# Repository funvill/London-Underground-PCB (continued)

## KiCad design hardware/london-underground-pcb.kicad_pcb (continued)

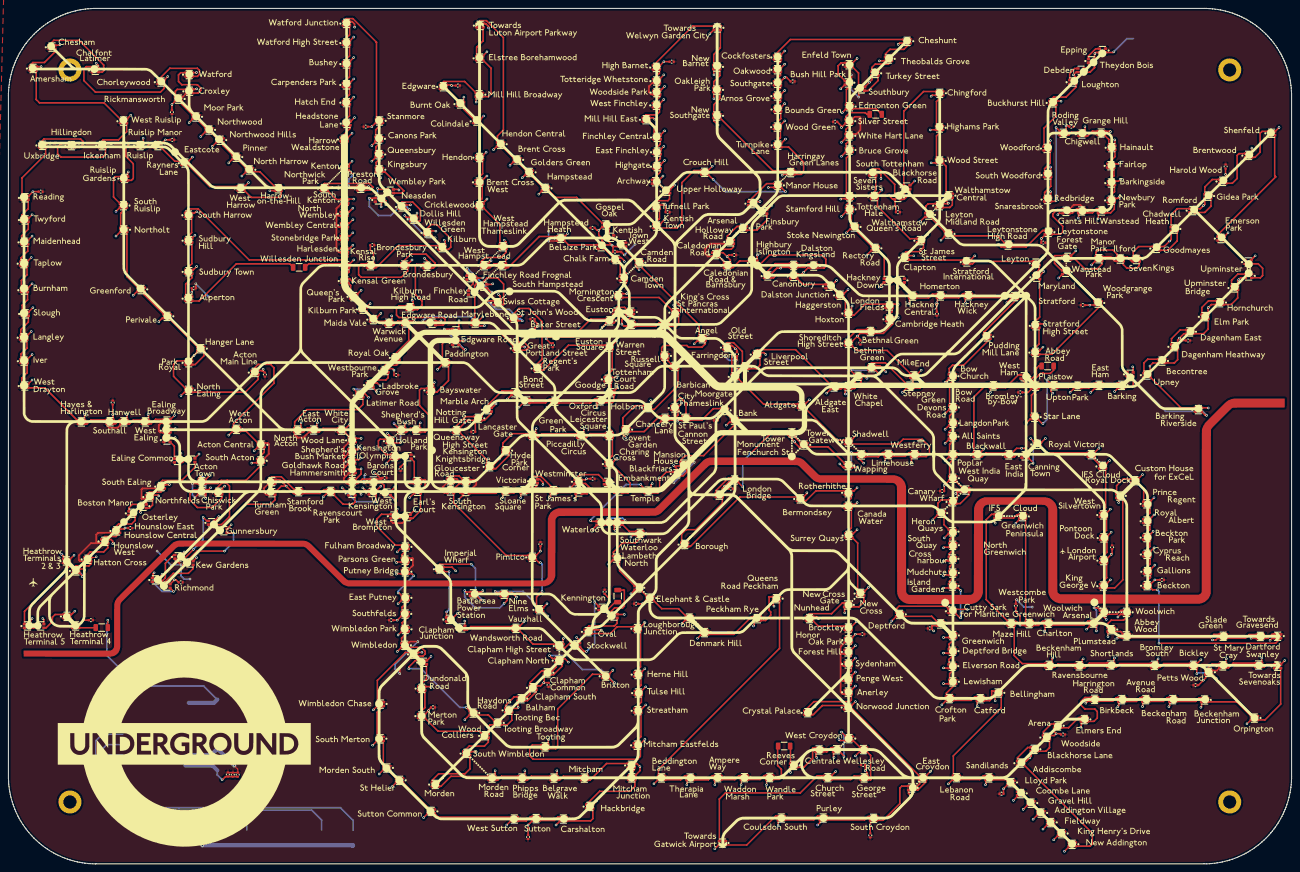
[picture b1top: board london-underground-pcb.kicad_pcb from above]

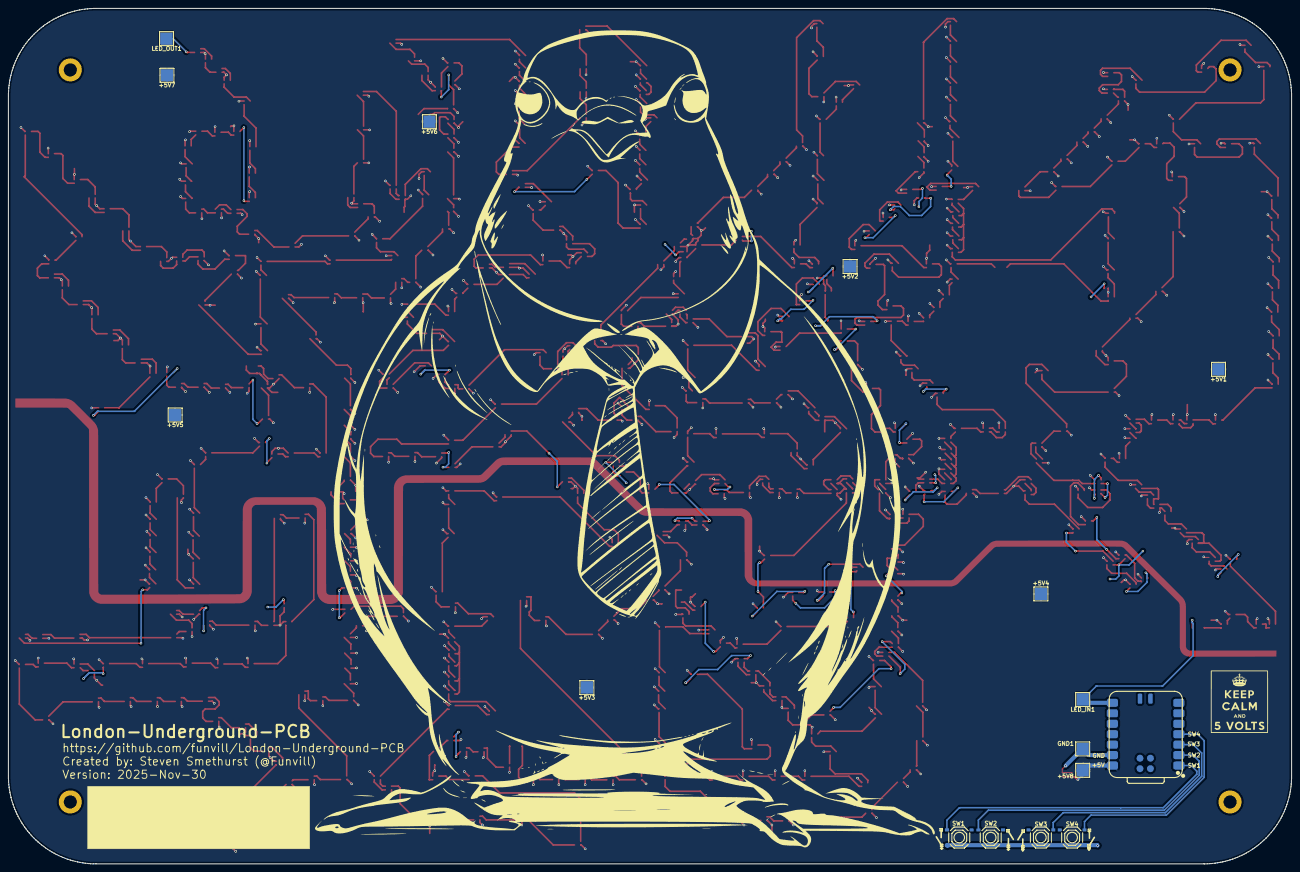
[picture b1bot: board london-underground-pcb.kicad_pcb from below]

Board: 2 copper layers, 312.0 x 208.0 mm, 655 parts (16 on the bottom side), 582 nets.

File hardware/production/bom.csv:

Designator,Footprint,Quantity,Value,LCSC Part #
"+5V1, +5V2, +5V3, +5V4, +5V5, +5V6, +5V7, +5V8, GND1, LED_IN1, LED_OUT1",TestPoint_Pad_3.0x3.0mm,11,TestPoint,
"LED1, LED10, LED100, LED101, LED102, LED103, LED104, LED105, LED106, LED107, LED108, LED109, LED11, LED110, LED111, LED112, LED113, LED114, LED115, LED116, LED117, LED118, LED119, LED12, LED120, LED121, LED122, LED123, LED124, LED125, LED126, LED127, LED128, LED129, LED13, LED130, LED131, LED132, LED133, LED134, LED135, LED136, LED137, LED138, LED139, LED14, LED140, LED141, LED142, LED143, LED144, LED145, LED146, LED147, LED148, LED149, LED15, LED150, LED151, LED152, LED153, LED154, LED155, LED156, LED157, LED158, LED159, LED16, LED160, LED161, LED162, LED163, LED164, LED165, LED166, LED167, LED168, LED169, LED17, LED170, LED171, LED172, LED173, LED174, LED175, LED176, LED177, LED178, LED179, LED18, LED180, LED181, LED182, LED183, LED184, LED185, LED186, LED187, LED188, LED189, LED19, LED190, LED191, LED192, LED193, LED194, LED195, LED196, LED197, LED198, LED199, LED2, LED20, LED200, LED201, LED202, LED203, LED204, LED205, LED206, LED207, LED208, LED209, LED21, LED210, LED211, LED212, LED213, LED214, LED215, LED216, LED217, LED218, LED219, LED22, LED220, LED221, LED222, LED223, LED224, LED225, LED226, LED227, LED228, LED229, LED23, LED230, LED231, LED232, LED233, LED234, LED235, LED236, LED237, LED238, LED239, LED24, LED240, LED241, LED242, LED243, LED244, LED245, LED246, LED247, LED248, LED249, LED25, LED250, LED251, LED252, LED253, LED254, LED255, LED256, LED257, LED258, LED259, LED26, LED260, LED261, LED262, LED263, LED264, LED265, LED266, LED267, LED268, LED269, LED27, LED270, LED271, LED272, LED273, LED274, LED275, LED276, LED277, LED278, LED279",LED-SMD_4P-L1.6-W1.5_XL-1615RGBC-WS2812B-1,200,XL-1615RGBC-WS2812B,C5349954
"LED28, LED280, LED281, LED282, LED283, LED284, LED285, LED286, LED287, LED288, LED289, LED29, LED290, LED291, LED292, LED293, LED294, LED295, LED296, LED297, LED298, LED299, LED3, LED30, LED300, LED301, LED302, LED303, LED304, LED305, LED306, LED307, LED308, LED309, LED31, LED310, LED311, LED312, LED313, LED314, LED315, LED316, LED317, LED318, LED319, LED32, LED320, LED321, LED322, LED323, LED324, LED325, LED326, LED327, LED328, LED329, LED33, LED330, LED331, LED332, LED333, LED334, LED335, LED336, LED337, LED338, LED339, LED34, LED340, LED341, LED342, LED343, LED344, LED345, LED346, LED347, LED348, LED349, LED35, LED350, LED351, LED352, LED353, LED354, LED355, LED356, LED357, LED358, LED359, LED36, LED360, LED361, LED362, LED363, LED364, LED365, LED366, LED367, LED368, LED369, LED37, LED370, LED371, LED372, LED373, LED374, LED375, LED376, LED377, LED378, LED379, LED38, LED380, LED381, LED382, LED383, LED384, LED385, LED386, LED387, LED388, LED389, LED39, LED390, LED391, LED392, LED393, LED394, LED395, LED396, LED397, LED398, LED399, LED4, LED40, LED400, LED401, LED402, LED403, LED404, LED405, LED406, LED407, LED408, LED409, LED41, LED410, LED411, LED412, LED413, LED414, LED415, LED416, LED417, LED418, LED419, LED42, LED420, LED421, LED422, LED423, LED424, LED425, LED426, LED427, LED428, LED429, LED43, LED430, LED431, LED432, LED433, LED434, LED435, LED436, LED437, LED438, LED439, LED44, LED440, LED441, LED442, LED443, LED444, LED445, LED446, LED447, LED448, LED449, LED45, LED450, LED451, LED452, LED453, LED454, LED455, LED456, LED457, LED458, LED459",LED-SMD_4P-L1.6-W1.5_XL-1615RGBC-WS2812B-1,200,XL-1615RGBC-WS2812B,C5349954
"LED46, LED460, LED461, LED462, LED463, LED464, LED465, LED466, LED467, LED468, LED469, LED47, LED470, LED471, LED472, LED473, LED474, LED475, LED476, LED477, LED478, LED479, LED48, LED480, LED481, LED482, LED483, LED484, LED485, LED486, LED487, LED488, LED489, LED49, LED490, LED491, LED492, LED493, LED494, LED495, LED496, LED497, LED498, LED499, LED5, LED50, LED500, LED501, LED502, LED503, LED504, LED505, LED506, LED507, LED508, LED509, LED51, LED510, LED511, LED512, LED513, LED514, LED515, LED516, LED517, LED518, LED519, LED52, LED520, LED521, LED522, LED523, LED524, LED525, LED526, LED527, LED528, LED529, LED53, LED530, LED531, LED532, LED533, LED534, LED535, LED536, LED537, LED538, LED539, LED54, LED540, LED541, LED542, LED543, LED544, LED545, LED546, LED547, LED548, LED549, LED55, LED550, LED551, LED552, LED553, LED554, LED555, LED556, LED557, LED558, LED559, LED56, LED560, LED561, LED562, LED563, LED564, LED565, LED566, LED567, LED568, LED569, LED57, LED58, LED59, LED6, LED60, LED61, LED62, LED63, LED64, LED65, LED66, LED67, LED68, LED69, LED7, LED70, LED71, LED72, LED73, LED74, LED75, LED76, LED77, LED78, LED79, LED8, LED80, LED81, LED82, LED83, LED84, LED85, LED86, LED87, LED88, LED89, LED9, LED90, LED91, LED92, LED93, LED94, LED95, LED96, LED97, LED98, LED99",LED-SMD_4P-L1.6-W1.5_XL-1615RGBC-WS2812B-1,169,XL-1615RGBC-WS2812B,C5349954
"R1, R2, R3, R4, R5, R6",1206,6,1206W4F0000T5E,C17888
"ROW1, ROW10, ROW11, ROW12, ROW13, ROW14, ROW15, ROW16, ROW17, ROW18, ROW19, ROW2, ROW20, ROW21, ROW22, ROW23, ROW24, ROW25, ROW26, ROW27, ROW28, ROW29, ROW3, ROW30, ROW31, ROW32, ROW33, ROW34, ROW35, ROW36, ROW37, ROW38, ROW39, ROW4, ROW40, ROW41, ROW42, ROW43, ROW44, ROW45, ROW46, ROW47, ROW48, ROW49, ROW5, ROW50, ROW51, ROW52, ROW53, ROW54, ROW55, ROW56, ROW57, ROW58, ROW59, ROW6, ROW60, ROW7, ROW8, ROW9",0402,60,"10uF,10V,X5R",C52923

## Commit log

2025-02-16 WIP: Getting the font size correct
2025-02-16 Moved some files around
2025-02-18 Updated the silkscreen in the PCB with larger font
2025-02-18 first 150 LEDS placed
2025-02-18 Placed 570 LEDS,
    Still need to do the routing
2025-02-21 Resolving DRC
2025-02-23 Updated parts list from JLCPCB
2025-02-23 Added underground logo and preview image
2025-02-24 Added bird logo to the back panel
2025-02-24 As manufactured with JLCPCB 2024-Feb-24
2025-11-26 2025-nov-25 - cleanup ready for review
2025-11-26 Added kicanvas preview
2025-12-01 Fixed "unconnected items" in PCB viewer
2025-12-01 Fixed schematic errors
2025-12-01 before trying to fix library issues
2025-12-01 submitted to JLCPCB 2025-Nov-30
2026-01-21 testing script for LEDs
2026-03-30 before letting Claude take an attempt at it
2026-03-30 AI assisted update of all the LEDs offsets. There's still some work to be done here, but at least all the stations are all proper.
